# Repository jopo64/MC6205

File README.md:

# MC6205
- code for driving a MC6205 with a russian 100x100 pixel plasma tube
- Eagle layout files
- hardware testing code
- weatherstation based on openweathermap.org
- to get full usage of the software, a hardware change must be made before
  - you need a custom eprom for having the ISO-Latin-1 characters

Arduino on ESP32-WROOM

# hackady.io
please see project details at https://hackaday.io/project/178954

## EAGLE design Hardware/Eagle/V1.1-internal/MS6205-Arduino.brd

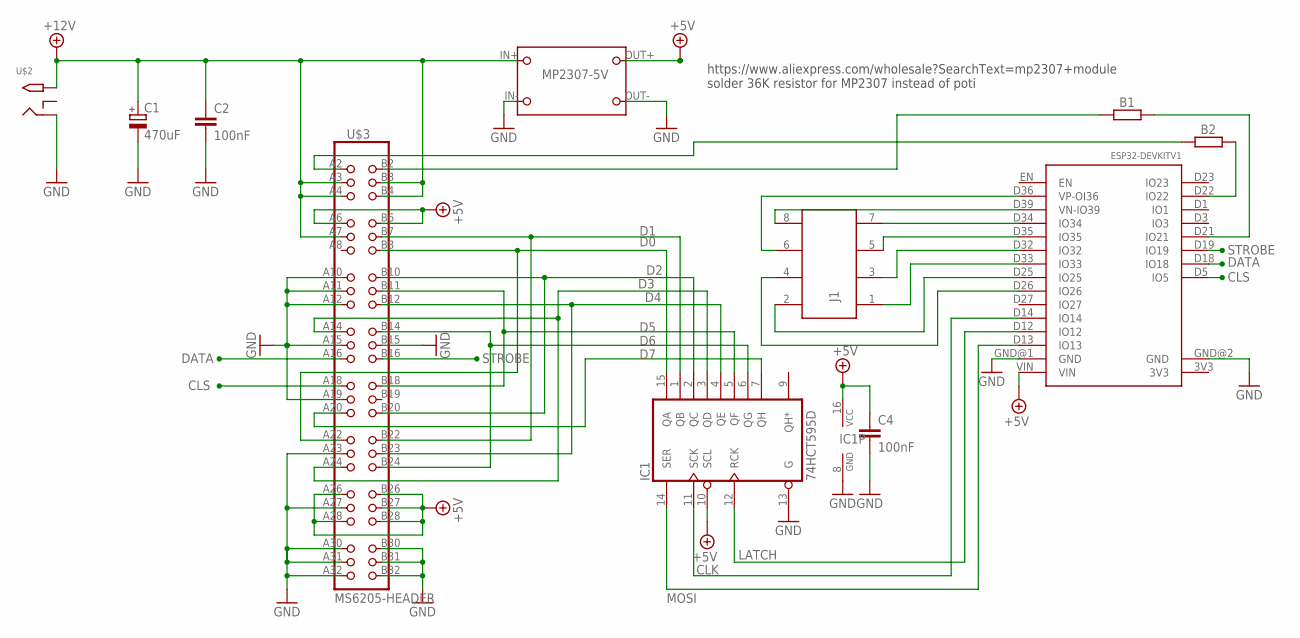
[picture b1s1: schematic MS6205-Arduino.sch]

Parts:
B1, B2: 0; 0204/5
C1: 470uF; 150CLZ-1010
C2: 100nF; C1206
C4: 100nF; C0805
IC1: 74HCT595D; SO16
J1: 61200822323
MP2307-5V: PWS-MP2307; MP2307-PWS
U$1: ESP32DEVKIT1-REDUCED; ESP32-DEVKIT1-REDUCED
U$2: 2.1MMJACKTHM; PJ-102A
U$3: MS6205-HEADER; MS6205_CONNECTOR_HOLE

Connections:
+12V: C1.+, C2.1, MP2307-5V.IN+, U$2.TIP, U$3.A3, U$3.A4, U$3.A7, U$3.B3, U$3.B4
CLK: IC1.11 (SCK), U$1.D14 (IO14)
CLS: U$1.D5 (IO5), U$3.A18
D0: IC1.15 (QA), U$3.A22, U$3.B8
D1: IC1.1 (QB), U$3.B7, U$3.B22
D2: IC1.2 (QC), U$3.B10, U$3.B20
D3: IC1.3 (QD), U$3.A14, U$3.A24
D4: IC1.4 (QE), U$3.B12, U$3.B23
D5: IC1.5 (QF), U$3.B11, U$3.B18
D6: IC1.6 (QG), U$3.B14, U$3.B24
D7: IC1.7 (QH), U$3.A20
DATA: U$1.D18 (IO18), U$3.A16
GND: C1.-, C2.2, C4.2, IC1.8 (GND), IC1.13 (G), MP2307-5V.IN-, MP2307-5V.OUT-, U$1.GND@1 (GND), U$1.GND@2 (GND), U$2.RING, U$3.A10, U$3.A11, U$3.A12, U$3.A15, U$3.A19, U$3.A23, U$3.A27, U$3.A30, U$3.A31, U$3.A32, U$3.B15, U$3.B30, U$3.B31, U$3.B32
LATCH: IC1.12 (RCK), U$1.D12 (IO12)
MOSI: IC1.14 (SER), U$1.D13 (IO13)
unnamed: B1.1, U$3.B2
unnamed: B2.1, U$3.A2
unnamed: B1.2, U$1.D21 (IO21)
unnamed: B2.2, U$1.D22 (IO22)
unnamed: J1.2, U$1.D25 (IO25)
unnamed: J1.1, U$1.D33 (IO33)
unnamed: J1.4, U$1.D26 (IO26)
unnamed: J1.3, U$1.D32 (IO32)
unnamed: J1.5, U$1.D35 (IO35)
unnamed: J1.7, U$1.D34 (IO34)
unnamed: J1.8, U$1.D39 (VN-IO39)
unnamed: J1.6, U$1.D36 (VP-OI36)
STROBE: U$1.D19 (IO19), U$3.B16
VCC: C4.1, IC1.10 (SCL), IC1.16 (VCC), MP2307-5V.OUT+, U$1.VIN, U$3.A6, U$3.A26, U$3.A28, U$3.B6, U$3.B26, U$3.B27, U$3.B28

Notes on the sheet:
https://www.aliexpress.com/wholesale?SearchText=mp2307+module solder 36K resistor for MP2307 instead of poti

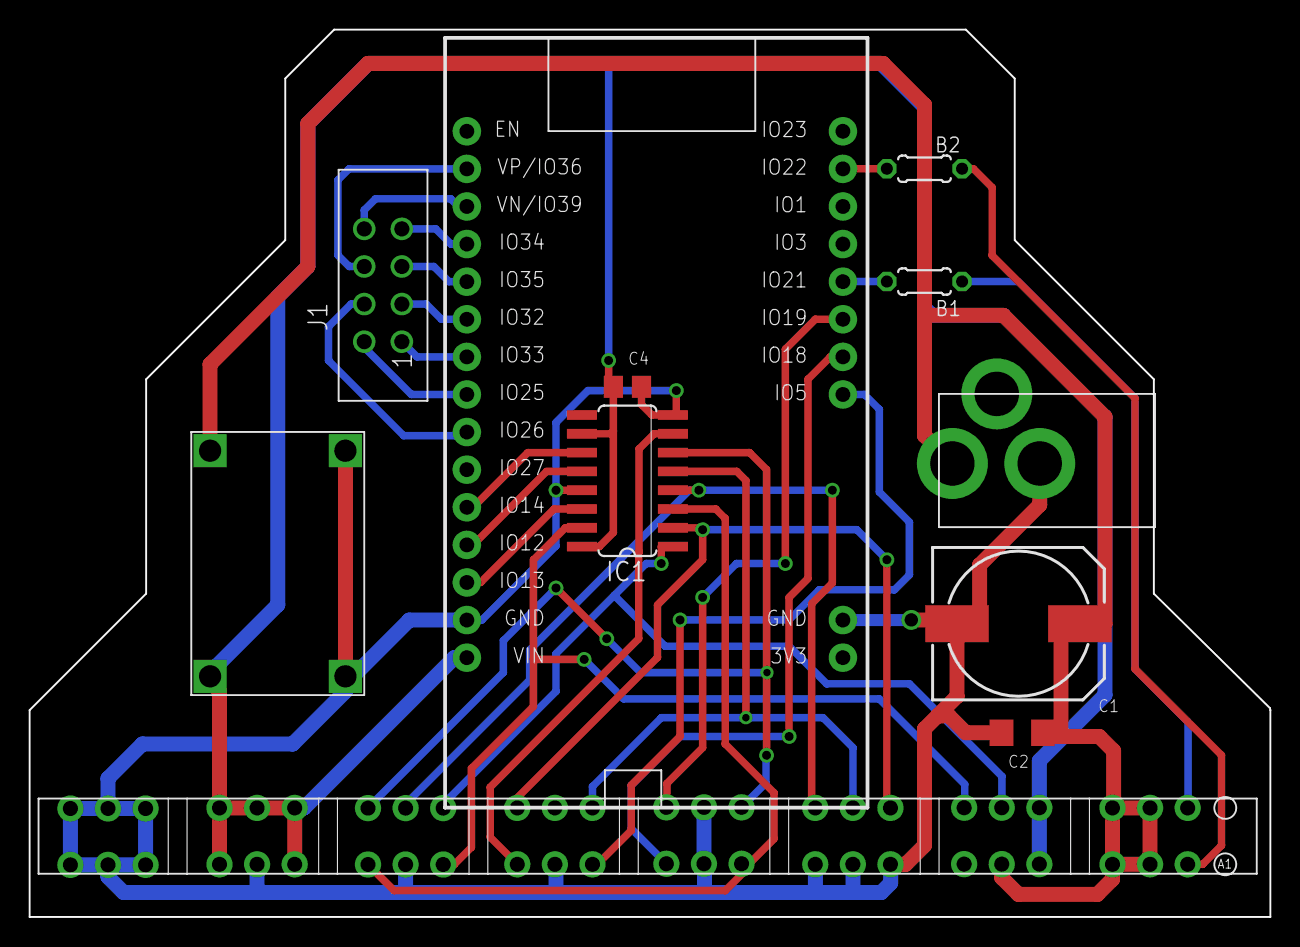
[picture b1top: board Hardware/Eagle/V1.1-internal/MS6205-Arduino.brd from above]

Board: 2 copper layers, 83.8 x 59.9 mm, 11 parts (0 on the bottom side), 29 nets.

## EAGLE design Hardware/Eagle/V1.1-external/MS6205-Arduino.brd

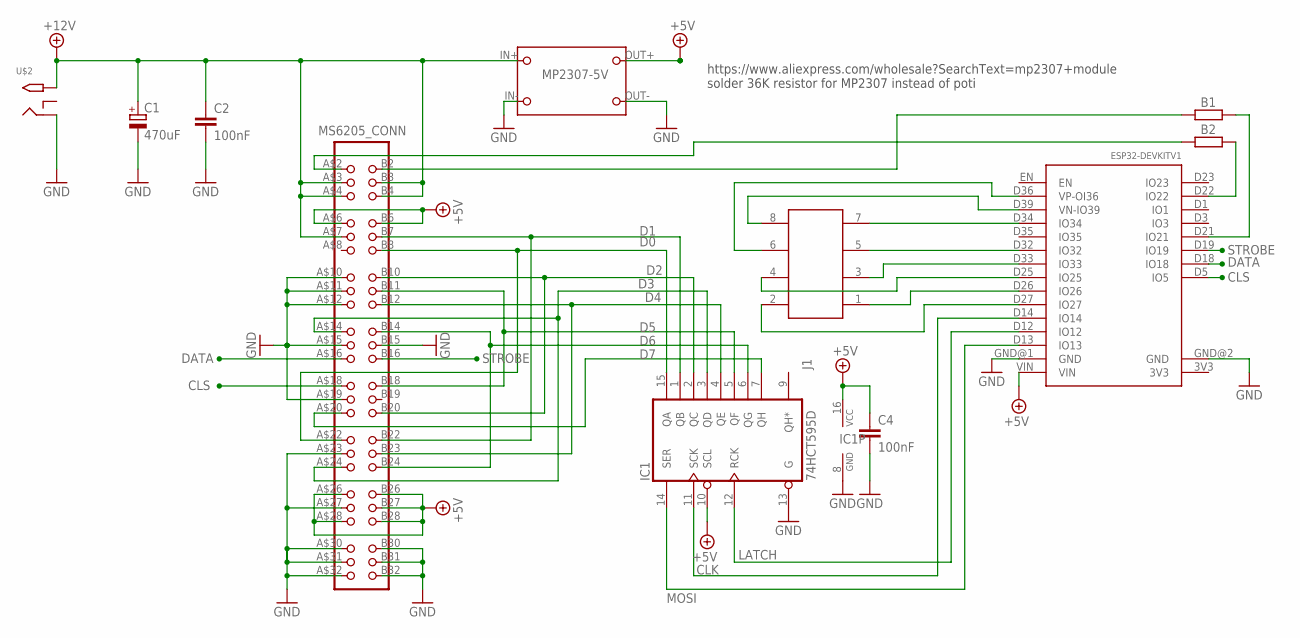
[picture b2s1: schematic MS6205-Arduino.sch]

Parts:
B1, B2: 0; 0204/5
C1: 470uF; 150CLZ-1010
C2, C4: 100nF; C0805
IC1: 74HCT595D; SO16
J1: 61200822323
MP2307-5V: PWS-MP2307; MP2307-PWS
U$1: ESP32DEVKIT1-REDUCED; ESP32-DEVKIT1-REDUCED
U$2: 2.1MMJACKTHM; PJ-102A
U$4: MS6205_CONN; MS6205_CONNECTOR_SMD

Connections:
+12V: C1.+, C2.1, MP2307-5V.IN+, U$2.TIP, U$4.A$3 (A3), U$4.A$4 (A4), U$4.A$7 (A7), U$4.B3, U$4.B4
CLK: IC1.11 (SCK), U$1.D14 (IO14)
CLS: U$1.D5 (IO5), U$4.A$18 (A18)
D0: IC1.15 (QA), U$4.A$22 (A22), U$4.B8
D1: IC1.1 (QB), U$4.B7, U$4.B22
D2: IC1.2 (QC), U$4.B10, U$4.B20
D3: IC1.3 (QD), U$4.A$14 (A14), U$4.A$24 (A24)
D4: IC1.4 (QE), U$4.B12, U$4.B23
D5: IC1.5 (QF), U$4.B11, U$4.B18
D6: IC1.6 (QG), U$4.B14, U$4.B24
D7: IC1.7 (QH), U$4.A$20 (A20)
DATA: U$1.D18 (IO18), U$4.A$16 (A16)
GND: C1.-, C2.2, C4.2, IC1.8 (GND), IC1.13 (G), MP2307-5V.IN-, MP2307-5V.OUT-, U$1.GND@1 (GND), U$1.GND@2 (GND), U$2.RING, U$4.A$10 (A10), U$4.A$11 (A11), U$4.A$12 (A12), U$4.A$15 (A15), U$4.A$19 (A19), U$4.A$23 (A23), U$4.A$27 (A27), U$4.A$30 (A30), U$4.A$31 (A31), U$4.A$32 (A32), U$4.B15, U$4.B30, U$4.B31, U$4.B32
LATCH: IC1.12 (RCK), U$1.D12 (IO12)
MOSI: IC1.14 (SER), U$1.D13 (IO13)
unnamed: B1.1, U$4.B2
unnamed: B2.1, U$4.A$2 (A2)
unnamed: B1.2, U$1.D21 (IO21)
unnamed: B2.2, U$1.D22 (IO22)
unnamed: J1.2, U$1.D27 (IO27)
unnamed: J1.1, U$1.D26 (IO26)
unnamed: J1.4, U$1.D25 (IO25)
unnamed: J1.3, U$1.D33 (IO33)
unnamed: J1.5, U$1.D32 (IO32)
unnamed: J1.7, U$1.D34 (IO34)
unnamed: J1.8, U$1.D39 (VN-IO39)
unnamed: J1.6, U$1.D36 (VP-OI36)
STROBE: U$1.D19 (IO19), U$4.B16
VCC: C4.1, IC1.10 (SCL), IC1.16 (VCC), MP2307-5V.OUT+, U$1.VIN, U$4.A$6 (A6), U$4.A$26 (A26), U$4.A$28 (A28), U$4.B6, U$4.B26, U$4.B27, U$4.B28

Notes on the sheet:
https://www.aliexpress.com/wholesale?SearchText=mp2307+module solder 36K resistor for MP2307 instead of poti

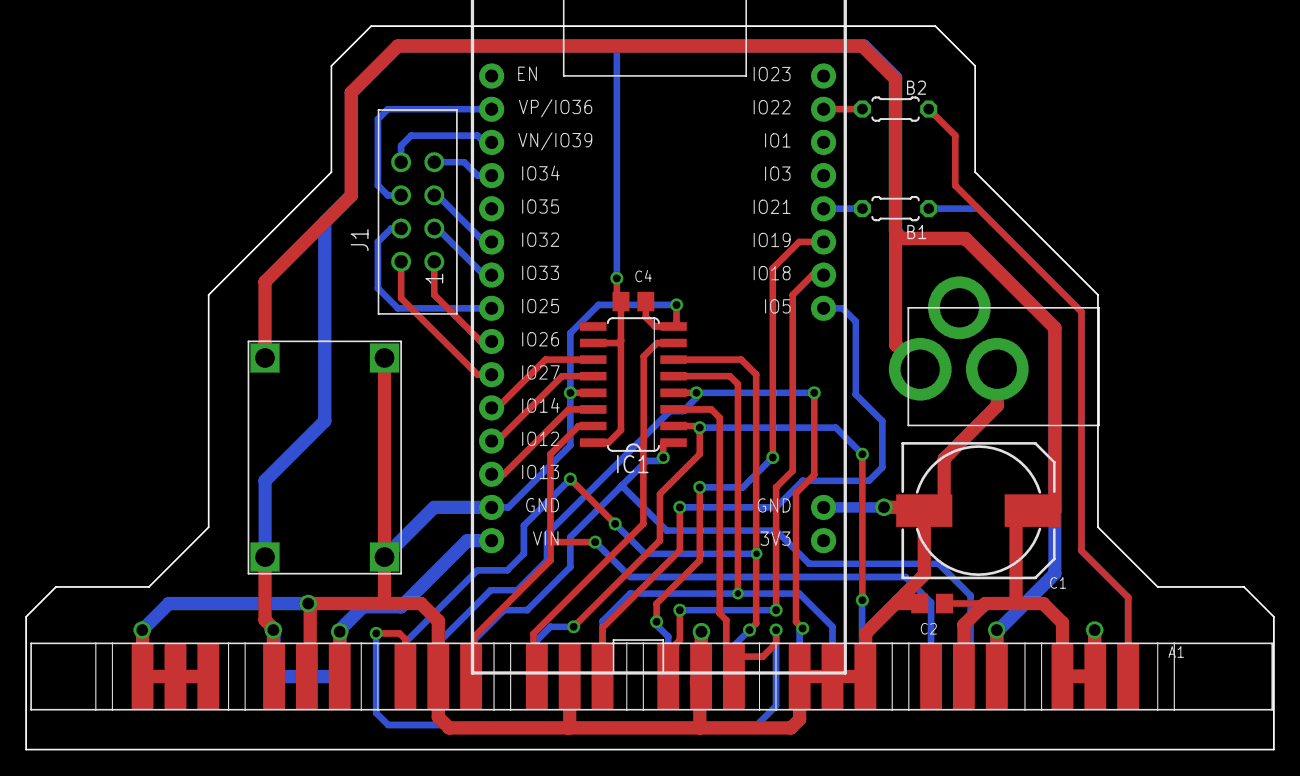
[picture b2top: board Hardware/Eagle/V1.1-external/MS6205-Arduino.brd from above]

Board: 2 copper layers, 95.5 x 55.4 mm, 11 parts (0 on the bottom side), 29 nets.

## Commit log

2021-05-16 initial weatherstation and hw-test code
2021-05-18 add hardware PCB schematics and Eagle files
2021-05-18 add picture of MC6205
2021-05-18 resize picture of MC6205
2021-05-18 small fix of port definitions
2021-05-18 small fix of port definition

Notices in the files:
parts and their libraries:
Wurth_Elektronik_Electromechanic_Wire_to: Copyright: Würth Elektronik
